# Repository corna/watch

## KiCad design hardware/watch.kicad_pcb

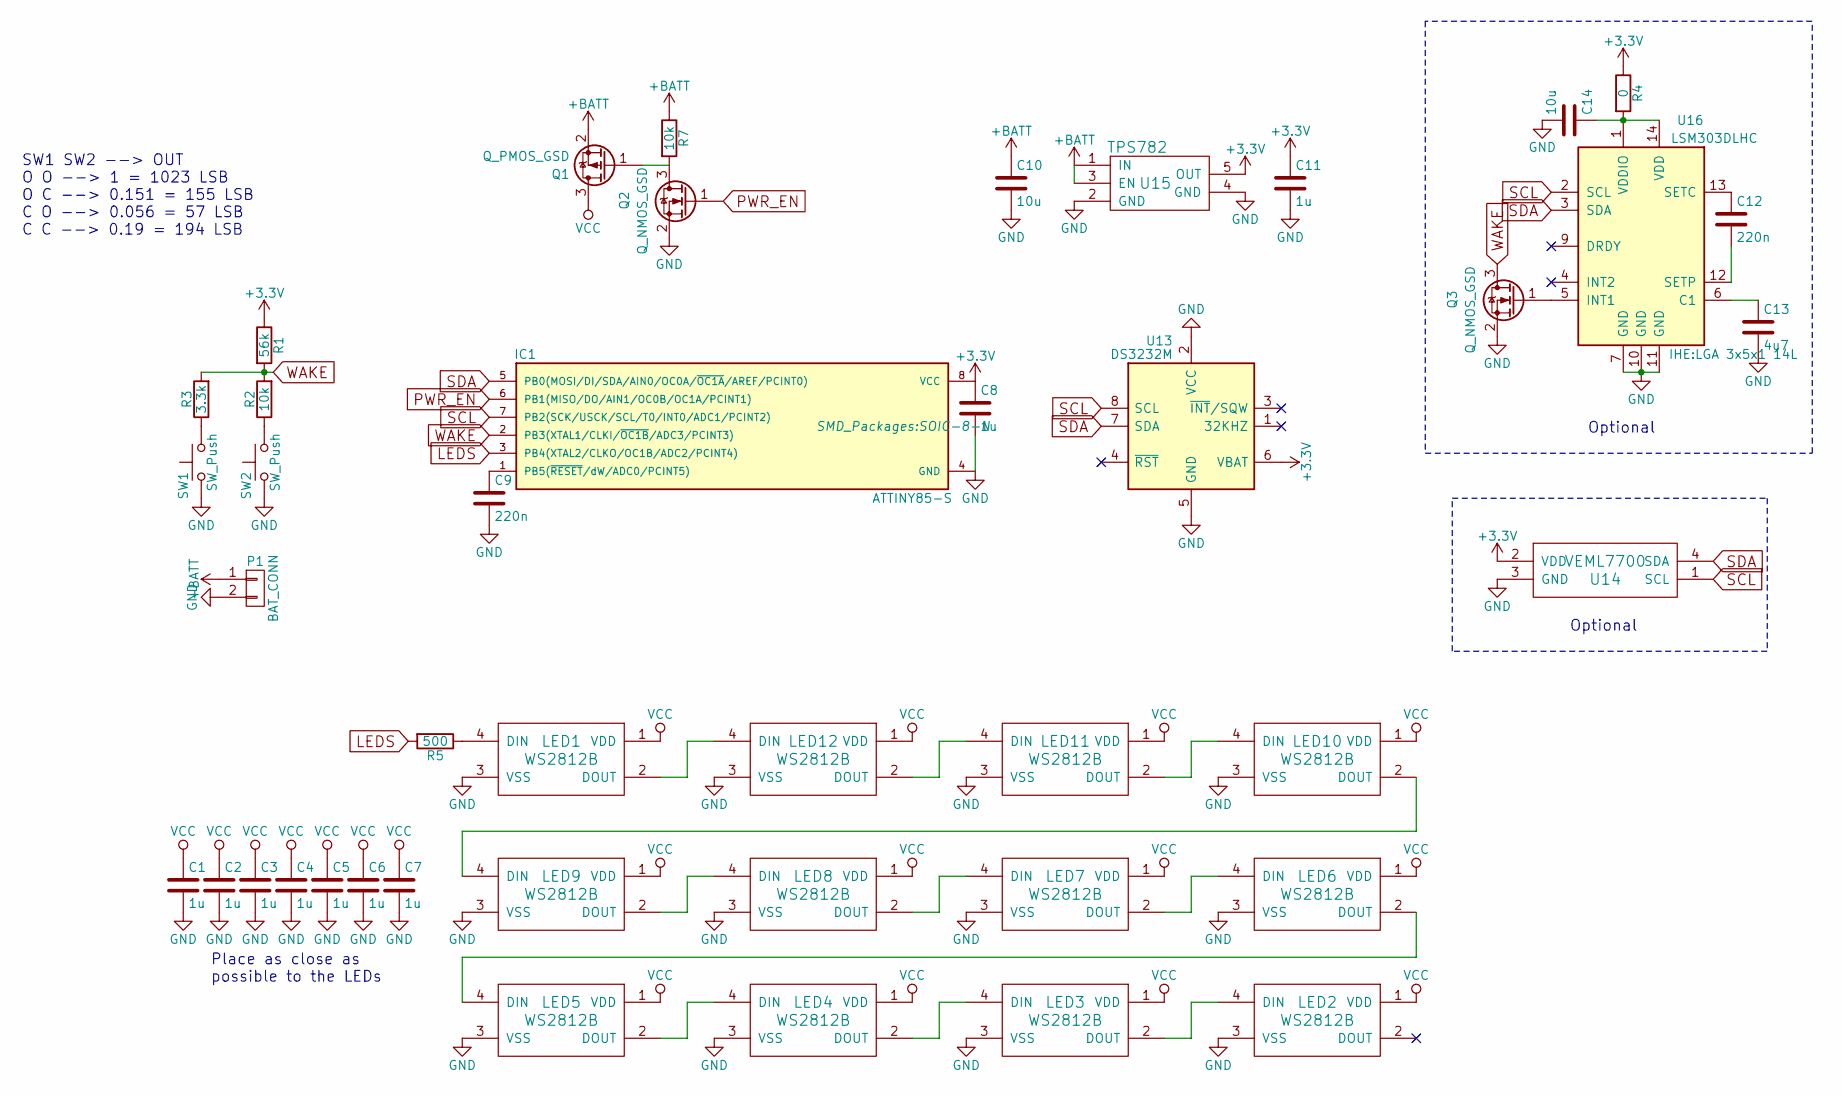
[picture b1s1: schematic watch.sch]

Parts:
C1, C2, C3, C4, C5, C6, C7, C8, C11: 1u; C_1206
C9, C12: 220n; C_1206
C10, C14: 10u; C_1206
C13: 4u7; C_1206
IC1: ATTINY85-S; SOIC-8-N
LED1, LED2, LED3, LED4, LED5, LED6, LED7, LED8, LED9, LED10, LED11, LED12: WS2812B; ws2812b
P1: BAT_CONN; Socket_Strip_Straight_1x02
Q1: Q_PMOS_GSD; SOT-23
Q2, Q3: Q_NMOS_GSD; SOT-23
R1: 56k; R_1206
R2, R7: 10k; R_1206
R3: 3.3k; R_1206
R4: 0; R_1206
R5: 500; R_1206
SW1, SW2: SW_Push; Side through-hole thin button
U13: DS3232M; SOIC-8_3.9x4.9mm_Pitch1.27mm
U14: VEML7700
U15: TPS782; SOT-23-5
U16: LSM303DLHC; LGA 3x5x1 14L

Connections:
+3V3: C8.1, C11.1, IC1.8 (VCC), R1.1, R4.1, U13.6 (VBAT), U14.2 (VDD), U15.5 (OUT)
+BATT: C10.1, P1.1, Q1.2 (S), R7.1, U15.1 (IN), U15.3 (EN)
GND: C1.2, C2.2, C3.2, C4.2, C5.2, C6.2, C7.2, C8.2, C9.2, C10.2, C11.2, C13.2, C14.2, IC1.4 (GND), LED1.3 (VSS), LED2.3 (VSS), LED3.3 (VSS), LED4.3 (VSS), LED5.3 (VSS), LED6.3 (VSS), LED7.3 (VSS), LED8.3 (VSS), LED9.3 (VSS), LED10.3 (VSS), LED11.3 (VSS), LED12.3 (VSS), P1.2, Q2.2 (S), Q3.2 (S), SW1.2, SW2.2, U13.2 (VCC), U13.5 (GND), U14.3 (GND), U15.2 (GND), U15.4 (GND), U16.7 (GND), U16.10 (GND), U16.11 (GND)
LEDS: IC1.3 (PB4(XTAL2/CLKO/OC1B/ADC2/PCINT4)), R5.2
unnamed: C9.1, IC1.1 (PB5(~RESET~/dW/ADC0/PCINT5))
unnamed: C12.1, U16.13 (SETC)
unnamed: C12.2, U16.12 (SETP)
unnamed: C13.1, U16.6 (C1)
unnamed: C14.1, R4.2, U16.1 (VDDIO), U16.14 (VDD)
unnamed: LED1.2 (DOUT), LED12.4 (DIN)
unnamed: LED1.4 (DIN), R5.1
unnamed: LED2.4 (DIN), LED3.2 (DOUT)
unnamed: LED3.4 (DIN), LED4.2 (DOUT)
unnamed: LED4.4 (DIN), LED5.2 (DOUT)
unnamed: LED5.4 (DIN), LED6.2 (DOUT)
unnamed: LED6.4 (DIN), LED7.2 (DOUT)
unnamed: LED7.4 (DIN), LED8.2 (DOUT)
unnamed: LED8.4 (DIN), LED9.2 (DOUT)
unnamed: LED9.4 (DIN), LED10.2 (DOUT)
unnamed: LED10.4 (DIN), LED11.2 (DOUT)
unnamed: LED11.4 (DIN), LED12.2 (DOUT)
unnamed: Q1.1 (G), Q2.3 (D), R7.2
unnamed: Q3.1 (G), U16.5 (INT1)
unnamed: R2.1, SW2.1
unnamed: R3.1, SW1.1
PWR_EN: IC1.6 (PB1(MISO/DO/AIN1/OC0B/OC1A/PCINT1)), Q2.1 (G)
SCL: IC1.7 (PB2(SCK/USCK/SCL/T0/INT0/ADC1/PCINT2)), U13.8 (SCL), U14.1 (SCL), U16.2 (SCL)
SDA: IC1.5 (PB0(MOSI/DI/SDA/AIN0/OC0A/~OC1A~/AREF/P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), U13.7 (SDA), U14.4 (SDA), U16.3 (SDA)
VCC: C1.1, C2.1, C3.1, C4.1, C5.1, C6.1, C7.1, LED1.1 (VDD), LED2.1 (VDD), LED3.1 (VDD), LED4.1 (VDD), LED5.1 (VDD), LED6.1 (VDD), LED7.1 (VDD), LED8.1 (VDD), LED9.1 (VDD), LED10.1 (VDD), LED11.1 (VDD), LED12.1 (VDD), Q1.3 (D)
WAKE: IC1.2 (PB3(XTAL1/CLKI/~OC1B~/ADC3/PCINT3)), Q3.3 (D), R1.2, R2.2, R3.2

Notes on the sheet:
Place as close as possible to the LEDs
SW1 SW2 --> OUT O O --> 1 = 1023 LSB O C --> 0.151 = 155 LSB C O --> 0.056 = 57 LSB C C --> 0.19 = 194 LSB
Optional

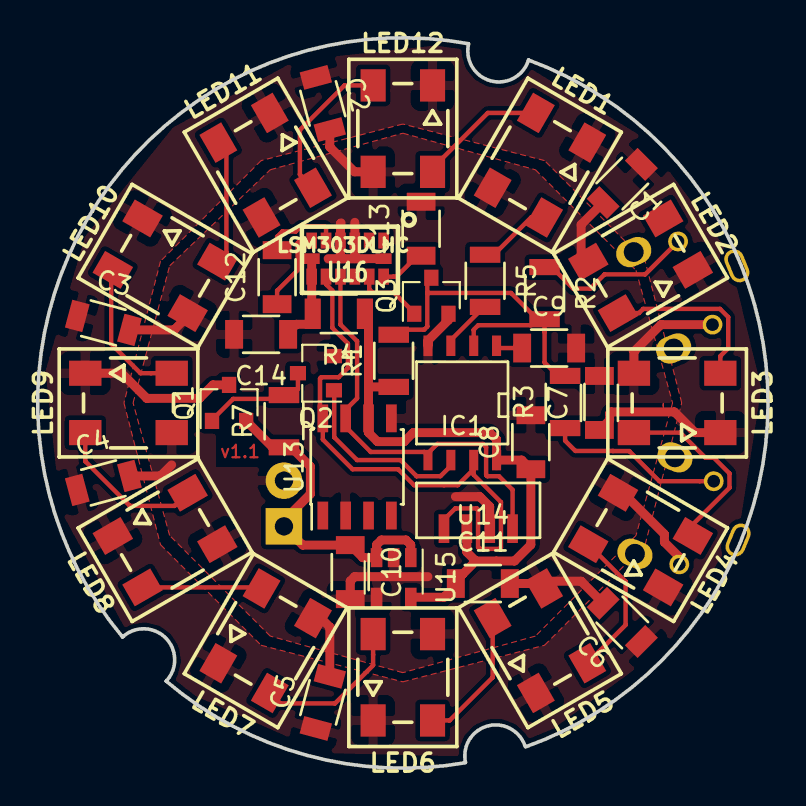
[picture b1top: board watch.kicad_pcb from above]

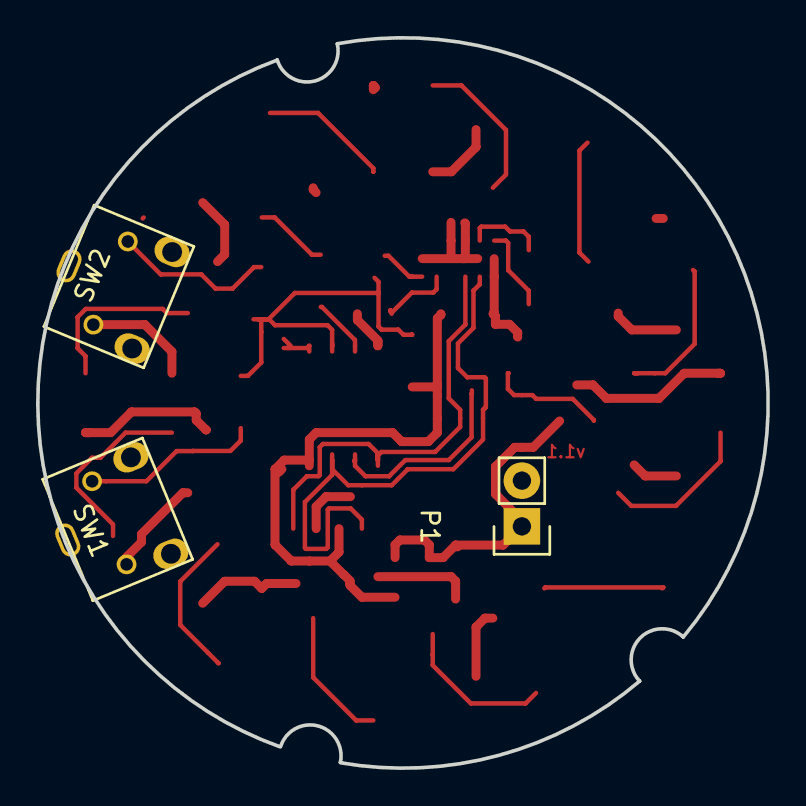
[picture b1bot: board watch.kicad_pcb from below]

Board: 2 copper layers, 40.6 x 40.6 mm, 43 parts (3 on the bottom side), 30 nets.

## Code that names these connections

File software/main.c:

#include <stdint.h>
#include <stdbool.h>

#include <avr/interrupt.h>
#include <avr/sleep.h>
#include <avr/pgmspace.h>
#include <util/delay.h>
#include <util/atomic.h>

#include "i2c.h"
#include "ws2812/ws2812_avr.h"
#include "veml7700/veml7700.h"

#define LIGHT_SENSOR_ADDR 0x20
#define AXEL_ADDR 0x32
#define MAGNETOMETER_ADDR 0x3c
#define RTC_ADDR 0x68

#define WAKE PINB3
#define PWR_EN PORTB1

#define WAKE_UNKNOWN 0
#define	WAKE_BUTTON1 1
#define WAKE_BUTTON2 2
#define WAKE_BOTH_BUTTONS (WAKE_BUTTON1 | WAKE_BUTTON2)
#define WAKE_AXEL 4

//LEDs start from LED1 (1/3 pi, 60°) and go counter-clockwise
struct cRGB leds[12] = {{ 0 }};

bool light_sensor_present;
bool axel_magnetometer_present;

uint16_t ambient_light;

//Returns the Vcc value in mV
uint16_t get_Vcc()
{
	ADMUX = _BV(MUX3) | _BV(MUX2);			//Vcc as reference, single-ended measure of Vbg, right adjust
	ADCSRA = _BV(ADEN);						//Turn on the ADC, auto trigger disabled, interrupt disabled, prescaler = 2
	_delay_ms(1);							//Wait for 1ms, as suggested by the datasheet
	ADCSRA |= _BV(ADIF) | _BV(ADSC);		//Clear the interrupt flag and start the conversion
	loop_until_bit_is_clear(ADCSRA, ADIF);	//Wait for the end of the measurement (max 6.25 us with 8MHz clock)
	ADCSRA &= ~_BV(ADEN);					//Turn off the ADC

	return (uint32_t)1100 * 1024 / ADC;
}

uint8_t get_wake_status()
{
	ADMUX = _BV(MUX1) | _BV(MUX0);			//Vcc as reference, single-ended measure of ADC3 (PB3), right adjust
	ADCSRA = _BV(ADEN);						//Turn on the ADC, auto trigger disabled, interrupt disabled, prescaler = 2
	ADCSRA |= _BV(ADIF) | _BV(ADSC);		//Clear the interrupt flag and start the conversion
	loop_until_bit_is_clear(ADCSRA, ADIF);	//Wait for the end of the measurement (max 6.25 us with 8MHz clock)
	ADCSRA &= ~_BV(ADEN);					//Turn off the ADC

	if (ADC < 25)
		return WAKE_AXEL;
	else if (ADC < 100)
		return WAKE_BUTTON1;
	else if (ADC < 175)
		return WAKE_BUTTON2;
	else if (ADC < 250)
		return WAKE_BOTH_BUTTONS;
	else
		return WAKE_UNKNOWN;
}

//Power down the AVR
//During power down the AVR can be waken up by PCINT, INT0, WDT or USI
void power_down()
{
	set_sleep_mode(SLEEP_MODE_PWR_DOWN);	//Set PWR_DOWN as sleep mode
    cli();							//Stop interrupts to ensure the BOD timed sequence executes as required
    sleep_enable();					//Set the SE bit
    sleep_bod_disable();			//Disable the BOD
    sei();							//Ensure interrupts enabled so we can wake up again
    sleep_cpu();					//Go to sleep

	sleep_disable();				//Wake up here
}

int main ()
{
	DDRB |= _BV(DDB1) | _BV(DDB4);	//PB1 and PB4 outputs; PB0, PB2 and PB3 inputs
	GIMSK = _BV(PCIE);				//Enable PCINT interrupts, disable INT0
	PCMSK = _BV(PCINT3);			//Enable PCINT3 interrupt (WAKE pin)
	i2c_init();

	PORTB |= _BV(PWR_EN);			//Power the LEDs

	sei();							//Enable the interrupts

	axel_magnetometer_present = i2c_detect(AXEL_ADDR);
	light_sensor_present = i2c_detect(LIGHT_SENSOR_ADDR);

	if (light_sensor_present)
		if (!veml7700_set(LIGHT_SENSOR_ADDR, true) || !veml7700_get(LIGHT_SENSOR_ADDR, &ambient_light))
			light_sensor_present = false;

	while (true) {
		//Magic

		power_down();				//Power down; after the wake ISR the program will resume the execution here
	}

	return 0;
}

//Button pressed or the axel triggered INT1
ISR(PCINT0_vect)
{
	if (bit_is_clear(PINB, WAKE))	{ //Ignore rising edges
	
	}
}

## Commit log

2017-05-12 Add fuse flashing
